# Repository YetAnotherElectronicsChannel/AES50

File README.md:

# AES50 VHDL IP
An implementation of the AES50 protocol in vanilla VHDL.

## About the IP
I started developing this IP around end of 2024 - originally with some other intention.   
However I decided to make this project public with the purpose to be used in the fabulous [OpenX32 project](https://github.com/OpenMixerProject/OpenX32).  
Therefore, this IP was developed fully independent/separated from the OpenX32 project and comes instead with a reference implementation on a custom PCB (also included in this repo) designed around an [Efinix Trion T20 FPGA](https://www.efinixinc.com/shop/t20.php).  
Integration into the OpenX32 project is still a to-do work.. But I'm sure those guys will manage :)

## AES50 Specification
Before asking any detailed questions about functionality or implementation of this IP, please make sure you read and understood the public available AES50 specification which can be downloaded [here](https://aes2.org/publications/standards-store/?id=45).    
Otherwise I might not answer to your request.

## Features of the IP
- Audio-Formats
  - 48kHz / 24-Bit
  - 44.1kHz / 24-Bit
- Audio-Interfaces
  - TDM-8 (6x In + 6x Out) for full 48x48 channel access
  - I2S (1x In + 1x Out) for a reduced 2x2 channel access (the other 46x46 channels are ignored)
- Support for Aux-Data-Tunnel (which is e.g. used for headamp control) over TDM or UART
  - Tunnels the auxiliary data channel through the TDM interface  
  - Send and receive data to/from the auxiliary data tunnel via UART 
- Operation Modes
  - AES50-Master + TDM/I2S Master (Timing Reference: Local Oscillator)
  - AES50-Master + TDM/I2S Slave  (Timing Reference: External I2S/TDM Device)
  - AES50-Slave  + TDM/I2S Master (Timing-Reference: External AES50 Device)
- PLL Support
  - Integrated I2C-controller and driver for Cirrus Logic CS2100CP PLL
- Compatibility / Real-Life Tested
  - Proven to work with X32, Wing, S- and DL- series stageboxes
  - Flawless handling of Cat-Cable Hot-Plugging

### IP Internal Structure    

### Use Case A: 48x48 Channel with Multi-TDM8 Interface and Aux-Data via Uart

### Use Case B: 2x2 Channel with simple I2S Interface and Aux-Data via Uart

### Use Case C: 48x48 Channel with Multi-TDM8 Interface and Aux-Data via TDM8

### Top-Module Ports Description
| Signal                     | Direction | Type                          | Description                             |
| -------------------------- | -------- | ------------------------------ | --------------------------------------- |
| **clk50_i**                | in       | `std_logic`                    | 50 MHz Clock for the Ethernet Logic     |
| **clk100_i**               | in       | `std_logic`                    | 100 MHz Clock for the Core Logic        |
| **rst_i**                  | in       | `std_logic`                    | Synchronous Reset (100 MHz clock-domain)|
| **fs_mode_i**              | in       | `std_logic_vector(1 downto 0)` | Sample-Rate Select<br><ul><li>00 → 44.1 kHz</li><li>01 → 48 kHz</li><li>10 → n.a.</li><li>11 → n.a.</li></ul>|
| **sys_mode_i**             | in       | `std_logic_vector(1 downto 0)` | System-Mode Select<br><ul><li>00 → AES50 Slave & I2S/TDM Master</li><li>01 → AES50 Master & I2S/TDM Master</li><li>10 → AES50 Master & I2S/TDM Slave</li><li>11 → n.a.</li></ul>|               |
| **tdm8_i2s_mode_i**        | in       | `std_logic`                    | Interface Select<br><ul><li>0 → 48x48 TDM8 (Support for Aux-over-TDM)</li><li>1 → 2x2 I2S (only Aux-over-UART)</li></ul>|
| **aux_tx_tdm_uart_select_i**| in       | `std_logic`                   | Aux-Data-Mode <br><ul><li>0 → Aux-over-TDM</li><li>1 → Aux-over-UART</li></ul>|
| **rmii_crs_dv_i**          | in       | `std_logic`                    | RMII Data Valid Receive from PHY        |
| **rmii_rxd_i**             | in       | `std_logic_vector(1 downto 0)` | RMII Data from PHY                      |
| **rmii_tx_en_o**           | out      | `std_logic`                    | RMII Data Valid Transmit to PHY         |
| **rmii_txd_o**             | out      | `std_logic_vector(1 downto 0)` | RMII Data to PHY                        |
| **phy_rst_n_o**            | out      | `std_logic`                    | PHY Reset (active low)                  |
| **aes50_clk_a_rx_i**       | in       | `std_logic`                    | AES50 Clock A Receive                   |
| **aes50_clk_a_tx_o**       | out      | `std_logic`                    | AES50 Clock A Transmit                  |
| **aes50_clk_a_tx_en_o**    | out      | `std_logic`                    | AES50 Clock A Enable LVDS Output Driver      |
| **aes50_clk_b_rx_i**       | in       | `std_logic`                    | AES50 Clock B Receive                   |
| **aes50_clk_b_tx_o**       | out      | `std_logic`                    | AES50 Clock B Transmit                  |
| **aes50_clk_b_tx_en_o**    | out      | `std_logic`                    | AES50 Clock B Enable LVDS Output Driver      |
| **clk_1024xfs_from_pll_i** | in       | `std_logic`                    | Clock from external PLL (1024× fs)      |
| **pll_lock_n_i**           | in       | `std_logic`                    | External PLL Lock Status (active low)   |
| **clk_to_pll_o**           | out      | `std_logic`                    | Clock to external PLL                   |
| **pll_mult_value_o**       | out      | `natural`                      | External PLL multiplication-factor      |
| **pll_init_busy_i**        | in       | `std_logic`                    | PLL init busy status                    |
| **mclk_o**                 | out      | `std_logic`                    | Master Clock (256x fs) - derived (divided by x4) from PLL - independent of System-Mode Select |
| **wclk_o**                 | out      | `std_logic`                    | Word Clock Output (if our IP is I2S/TDM Master)   |
| **bclk_o**                 | out      | `std_logic`                    | Bit Clock Output  (if our IP is I2S/TDM Master)   |
| **wclk_readback_i**        | in       | `std_logic`                    | Word Clock Readback (direct from FPGA-Pin - always needed)    |
| **bclk_readback_i**        | in       | `std_logic`                    | Bit Clock Readback (direct from FPGA-Pin - always needed)     |
| **wclk_out_en_o**          | out      | `std_logic`                    | Word Clock Output Enable (high if IP is I2S/TDM Master)    |
| **bclk_out_en_o**          | out      | `std_logic`                    | Bit Clock Output Enable (high if IP is I2S/TDM Master)     |
| **tdm_i**                  | in       | `std_logic_vector(6 downto 0)` | 6x TDM8 Data Input + 1x TDM8 Aux Data Input   (only needed in 48x48 mode)               |
| **tdm_o**                  | out      | `std_logic_vector(6 downto 0)` | 6x TDM8 Data Output + 1x TDM8 Aux Data Output   (only needed in 48x48 mode)                    |
| **i2s_i**                  | in       | `std_logic`                    | I2S Input  (only needed in 2x2 mode)                            |
| **i2s_o**                  | out      | `std_logic`                    | I2S Output (only needed in 2x2 mode)                             |
| **aes_ok_o**               | out      | `std_logic`                    | AES50 Link Status  (high when connection established)         |
| **dbg_o**                  | out      | `std_logic_vector(7 downto 0)` | Various internal debug signals                          |
| **uart_o**               	 | out      | `std_logic`                    | UART output (received data from the AES50 AUX tunnel)     |
| **uart_i**               	 | in      | `std_logic`                     | UART input (data to send over AES50 AUX-tunnel)     |
### Aux Data Tunnel
AES50 provides (as part of the protocol) an auxiliary data channel with a fixed bandwidth of roughly 5 Mbit/s (the exact rate depends on the selected sample rate, as the auxiliary data stream is synchronous with the audio transmission).  
According to the AES50 specification, there was a proposal (though not mandatory) to use standard Ethernet frames that could be tunneled through this auxiliary data channel - (ever wondered about the mysterious Ethernet port on the DN9630?) -> Therefore I assume that this proposed approach using virtual Ethernet frames is also used in other AES50 devices on the market.  
However, additional mechanisms are required to transmit Ethernet frames through the auxiliary channel - specifically bit-stuffing and data-scrambling. 

#### Aux Data over TDM  
Since the bitstream is synchronous with the audio transmission, this IP enables sending and receiving the aux-bitstream over the TDM8 interface.  
Internally, the IP handles the bitstream as 16-bit words, and the TDM module distributes the auxiliary data evenly across the eight TDM slots as 24-bit “samples.”  
The extra 8 bits act as an overlay protocol to ensure correct interpretation of the auxiliary words when tunneling them over a 3rd party audio-transportation-medium.  
If the TDM-Aux-RX/TX pins of two instances of this IP are cross-connected, it allows transparent tunneling of the auxiliary data channel as long as synchronicity and bit-consistency is ensured.  
A similar concept appears to be implemented in the Appsys Multiverter, which tunnels AES50 auxiliary data as eight audio channels through a Dante network to maintain head-amp remote control.

- See further details in the TDM module implementation

#### Aux Data over UART
It is also possible to send and receive data over the aux-data-tunnel with a UART connection.         
See here an example print-out of a Wing-Rack connected.    

#### Head Amp Remote Control Example
A small [Arduino example](RPI_Pico_2040_HA_Remote_Example/RPI_Pico_2040_HA_Remote_Example.ino) shows how to self-identify and remotely control the head amps (gain & phantom power) of AES50 devices.

This example uses a Raspberry Pi Pico (RP2040), which acts as a command bridge between a computer and the UART terminal connected to the FPGA/AES50 IP core.  
The device identifies itself as an X32 Full-Size and the head amps can be controlled via a serial terminal using the following command examples:

- `gain:ch1@20` → Sets gain on channel 1 to +20 dB  
- `phantom:ch5@1` → Enables +48V on channel 5  
- `phantom:ch5@0` → Disables +48V on channel 5  

The gain-ranges may be interpreted differently with different devices. You will find some info in the comments of the code-example.  
This example is currently configured for controlling a Wing. Make sure that Remote-HA-Control over AES50 is enabled in the console settings.  

See more information here: [Unofficial Protocol Description](Doc/Unofficial_AES50_AUX_Protocol_for_MusicGroup_Devices.pdf)  

Special thanks to Christian Nöding for reverse-engineering the proprietary protocol and Thomas Zint (Behringer R&D) for helping with the checksum calculation.  

Note: The transmission of channel-names does not work yet.

### Audio Interface Timing

Warning: When this IP is in I2S/TDM slave-mode (sys_mode_i = "10"), make ultimately sure, that BCLK/WCLK is stable before releasing the IP's reset.  
AES50 protocol has a pulse-width modulation mechanism in the outgoing (LVDS-)clock signals which needs to be synchronized to the incoming I2S/TDM clock.  
This is only done once after reset. You must ensure externally, if WCLK/BCLK has changed or was unstable, this IP core runs again through a new reset.

#### I2S
In I2S mode, BCLK is 64*fs : 32-Bit per Slot (24-Bit Audio + 8 Bit Padding).  
3.072 MHz for 48k mode and 2.8224 MHz for 44k1. No other I2S configuration is supported besides this.  
This is valid for all system-modes.

#### TDM-8
BCLK is supposed to be 12.288 MHz for 48k or 11.2896 MHz for 44k1 : 32-Bit per Slot (24-Bit Audio + 8 Bit Padding).  
No other TDM configuration is supported besides this.  
This is valid for all system-modes.

#### TDM-8 Master Timing (when BCLK/WCLK is output)
When the IP is TDM master, the WCLK will be high for 8 BCLK cycles. 

#### TDM-8 Slave Timing (when BCLK/WCLK is input)
WCLK must be only high for one BCLK pulse (but can be longer of course)

### Misc
#### Deviations against the specification
- Bit-Error correction is only implemented on the transmitting side (as AES50 devices on market expects this to be implemented properly), however this IP does not correct bit-errors on receiving side. (I personally don't see this as a critical feature. Basically no other network audio protocol has this implemented)
- AES50 specifies a delay of around 3 sample times IP in- to output (in 44k1, 48k). However this IP processes the audio-samples internally in frames of 6 samples at 48k or 11 samples at 44k1. Therefore the latency is slightly higher
- Clock integrity check: AES50 by default runs the LVDS-clock-signals (through the CAT-wire) bidirectional. Even though it would be technically enough to run the clock only unidrectional from the clock-master to the clock-slave, AES50 uses this to check the integrity of the clock-recovery (PLL) on the AES50-slave-device side. As I understood, the slave-device would be supposed to regenerate the pulse-width modulated clock signal based on the recovered clock and send it back to the master. However this IP just loops the clock back to the master in case it is in slave-configuration. Also as per spec, the AES50 should verify the clock speeds for correctness. This IP has implemented only a more simple timeout-watchdog alike clock integrity checking (on both clock-transmitting and clock-receiving side).
- AES50 also supports other audio-formats and sample-rates (e.g. Bitstream-Audio, 88k2, 96k, etc..). This IP is only usable for 24-Bit PCM-Audio for 44k1 and 48k. However the IP is prepared for later integration of 88k2 and 96k sample-rate. I just didn't do this because I was lacking of suitable devices which support AES50 with 88k2/96k.
- The original AES50 implementation found in commercial devices also seem to differ against the specification (or I understood the specification wrong) in two points I found out so far (by actually reverse engineering it):
  -  The figures for aux-data-packet scrambler / descrambler in the specification seem to be exchanged against each other. The actual data-scrambler is the logic-structure shown in the descrambler-figure and vice-versa
  -  In 48k mode, one LC-segment (352 Bits) should consist of in sum 12 LC-sub-segments with two multiplexed channels of 6 samples each having 2-bit padding after each LC-subsegment and 4-bit padding at the end of the LC-frame.  According to my calculations, one LC-subsegment should be 27-bits long (12* (27Bit LC-Subsegment + 2-Bit Padding))+4-Bit Padding = 352 Bit. However the actual protocol behaves like: (6* (26-Bit LC-Subsegment + 2-Bit Padding + 28-Bit LC-Subsegment + 2-Bit Padding)) + 4-Bit Padding = 352 Bit.

#### TODOs / next steps / not done yet
- Verification of internal clock domain crossings
- Constraining and verification of input- & output timings (RMII, TDM, etc..)
- Bit Transparency Testing
- Refactoring of TDM SerDes
- Implement 88k2/96k mode
- Check why the Arduino Code-Example is not transmitting channel-names correctly.
  
#### Random Info
- The core-clock of this IP can also run at a reduced clock-speed of 80 MHz (instead of 100 MHz) if I2S mode only is used. Some internal timing-reference values must be changed for this (see in the top VHDL module in the efinity project)
- In case, the IP will be used in sys_mode_i="01" (AES-master + TDM/I2S master) only, the external PLL is not necessarily needed and the IP can be tricked to run from a static oscilator with 1024xfs speed.   Connect the static 1024xfs clock to "clk_1024xfs_from_pll_i", make "pll_init_busy_i" and "pll_lock_n_i" to static '0' and just leave "clk_to_pll_o" and "pll_mult_value_o" open.
- sys_mode_i, fs_mode_i and tdm8_i2s_mode_i should not be changed on the fly. If this is changed, the IP needs a new reset.
- Spot the easter-egg in this project :-)

## Test Board Setup
### Overview
In I2S mode, only I0/O0 will be used as in+out.  

### Front View

### FPGA Resource Utilization
This is the resource utilization for a full configuration (all sample-rates and operation modes supported, dual TDM/I2S support, PLL-I2C driver etc.).  
Resource utilization depends on actual used configuration.  
Especially if core is configured for e.g. I2S only operation, the utilization is reduced drastically (the TDM-Serdes is still a rather resource-inefficient implementation as of today).

Reference FPGA: Efinix Trion T20Q100F3 (Speedgrade: 4) using Efinity 2025.1.110.5.9 toolchain.  

## Some technical implementation hints

### Ram Reorder processes in AES50-TX/RX Modules

### Startup Sequencing  
The Startup Sequencing must be timed very precisely.  
The Ethernet frame containing the "2048x ASSM-marker" in the header must be tightly aligned with the modulated-clock-pulses on the LVDS signaling.  
This happens in 48k as follows: The IP waits until the clock-pulse-modulation happens. (It is assumed it will happen again after 2048x WCLK). When the clock-pulse-modulation happened, a timer starts with the duration of approx. 2042x (2048-6) WCLK timeframes.  
Then the TDM-serializer starts recording samples into the FIFO to the AES50-TX-module.  
The AES50-TX-Module waits until 6 samples (basically 288 samples as it is 6 samples * 48 channels) are in the FIFO.  
The first ethernet-frame transmitted after this startup-sequence will contain the ASSM-marker in the frame-header and will be aligned with the 2048x modulated clock-pulse.  
This also explains the mysterious "first_transmit_counter" values on the top-level files.   
  
In 44k1 the same mechanism applies, but with a duration of 2048-11 = 2037 WCLK cycles wait time.

### Testbenches
I also attached now the testbenches I used.  
Please see the testbenches as WIP as I modified them as needed and those testbenches might not work out of the box. So this is more of a "playground" rather than a professional verification testbench.

## License

Copyright (c) 2025 Markus Noll (YetAnotherElectronicsChannel)

This IP core is free software: you can redistribute it and/or modify
it under the terms of the GNU General Public License as published by
the Free Software Foundation, either version 3 of the License, or
(at your option) any later version.

This IP core is distributed in the hope that it will be useful,
but WITHOUT ANY WARRANTY; without even the implied warranty of
MERCHANTABILITY or FITNESS FOR A PARTICULAR PURPOSE. See the
GNU General Public License for more details.

You should have received a copy of the GNU General Public License
along with this IP core. If not, see <https://www.gnu.org/licenses/>.

Any other use — including use in other projects or commercial applications —
is not permitted without a separate written license agreement.

Third-party components included in this repository may be licensed under
different terms (for example, GPLv3). These components retain their
original licenses and are clearly marked in the source header.

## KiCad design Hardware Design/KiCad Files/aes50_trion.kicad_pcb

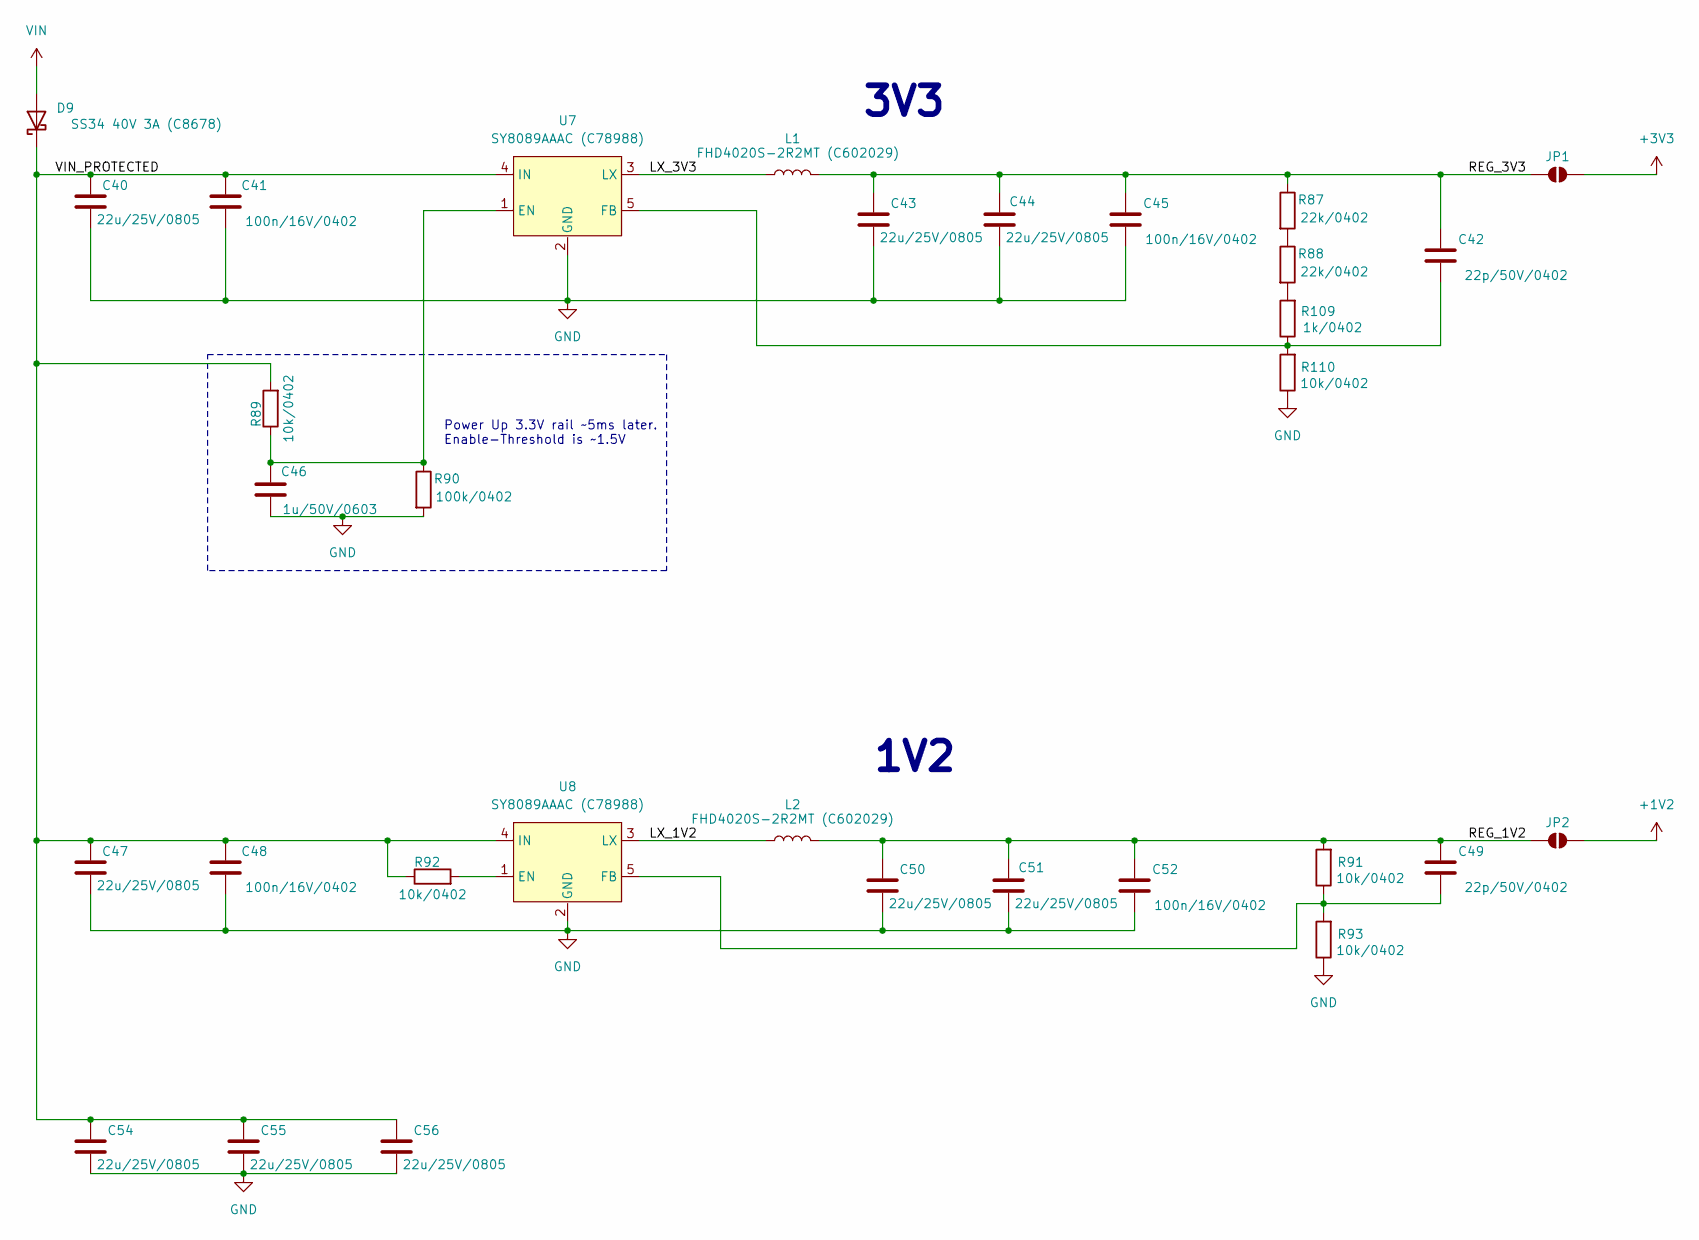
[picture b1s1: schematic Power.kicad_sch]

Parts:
C40, C43, C44, C47, C50, C51, C54, C55, C56: 22u/25V/0805; C_0805_2012Metric
C41, C45, C48, C52: 100n/16V/0402; C_0402_1005Metric
C42, C49: 22p/50V/0402; C_0402_1005Metric
C46: 1u/50V/0603; C_0603_1608Metric
D9: SS34 40V 3A (C8678); D_SMA
JP1, JP2: SolderJumper_2_Open; SolderJumper-2_P1.3mm_Open_RoundedPad1.0x1.5mm
L1, L2: FHD4020S-2R2MT (C602029); L_APV_ANR4020
R87, R88: 22k/0402; R_0402_1005Metric
R89, R91, R92, R93, R110: 10k/0402; R_0402_1005Metric
R90: 100k/0402; R_0402_1005Metric
R109: 1k/0402; R_0402_1005Metric
U7, U8: SY8089AAAC (C78988); SOT-23-5

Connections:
+1V2: JP2.2 (B); also elsewhere on the board
+3V3: JP1.2 (B); also elsewhere on the board
/Power/LX_1V2: L2.1, U8.3 (LX)
/Power/LX_3V3: L1.1, U7.3 (LX)
/Power/REG_1V2: C49.1, C50.1, C51.1, C52.1, JP2.1 (A), L2.2, R91.2
/Power/REG_3V3: C42.1, C43.1, C44.1, C45.1, JP1.1 (A), L1.2, R87.1
/Power/VIN_PROTECTED: C40.1, C41.1, C47.1, C48.1, C54.1, C55.1, C56.1, D9.1 (K), R89.2, R92.1, U7.4 (IN), U8.4 (IN)
GND: C40.2, C41.2, C43.2, C44.2, C45.2, C46.1, C47.2, C48.2, C50.2, C51.2, C52.2, C54.2, C55.2, C56.2, R90.2, R93.1, R110.1, U7.2 (GND), U8.2 (GND); also elsewhere on the board
unnamed: R87.2, R88.1
unnamed: R88.2, R109.2
unnamed: C46.2, R89.1, R90.1, U7.1 (EN)
unnamed: C42.2, R109.1, R110.2, U7.5 (FB)
unnamed: R92.2, U8.1 (EN)
unnamed: C49.2, R91.1, R93.2, U8.5 (FB)
VIN: D9.2 (A); also elsewhere on the board

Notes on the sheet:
3V3
1V2
Power Up 3.3V rail ~5ms later. Enable-Threshold is ~1.5V

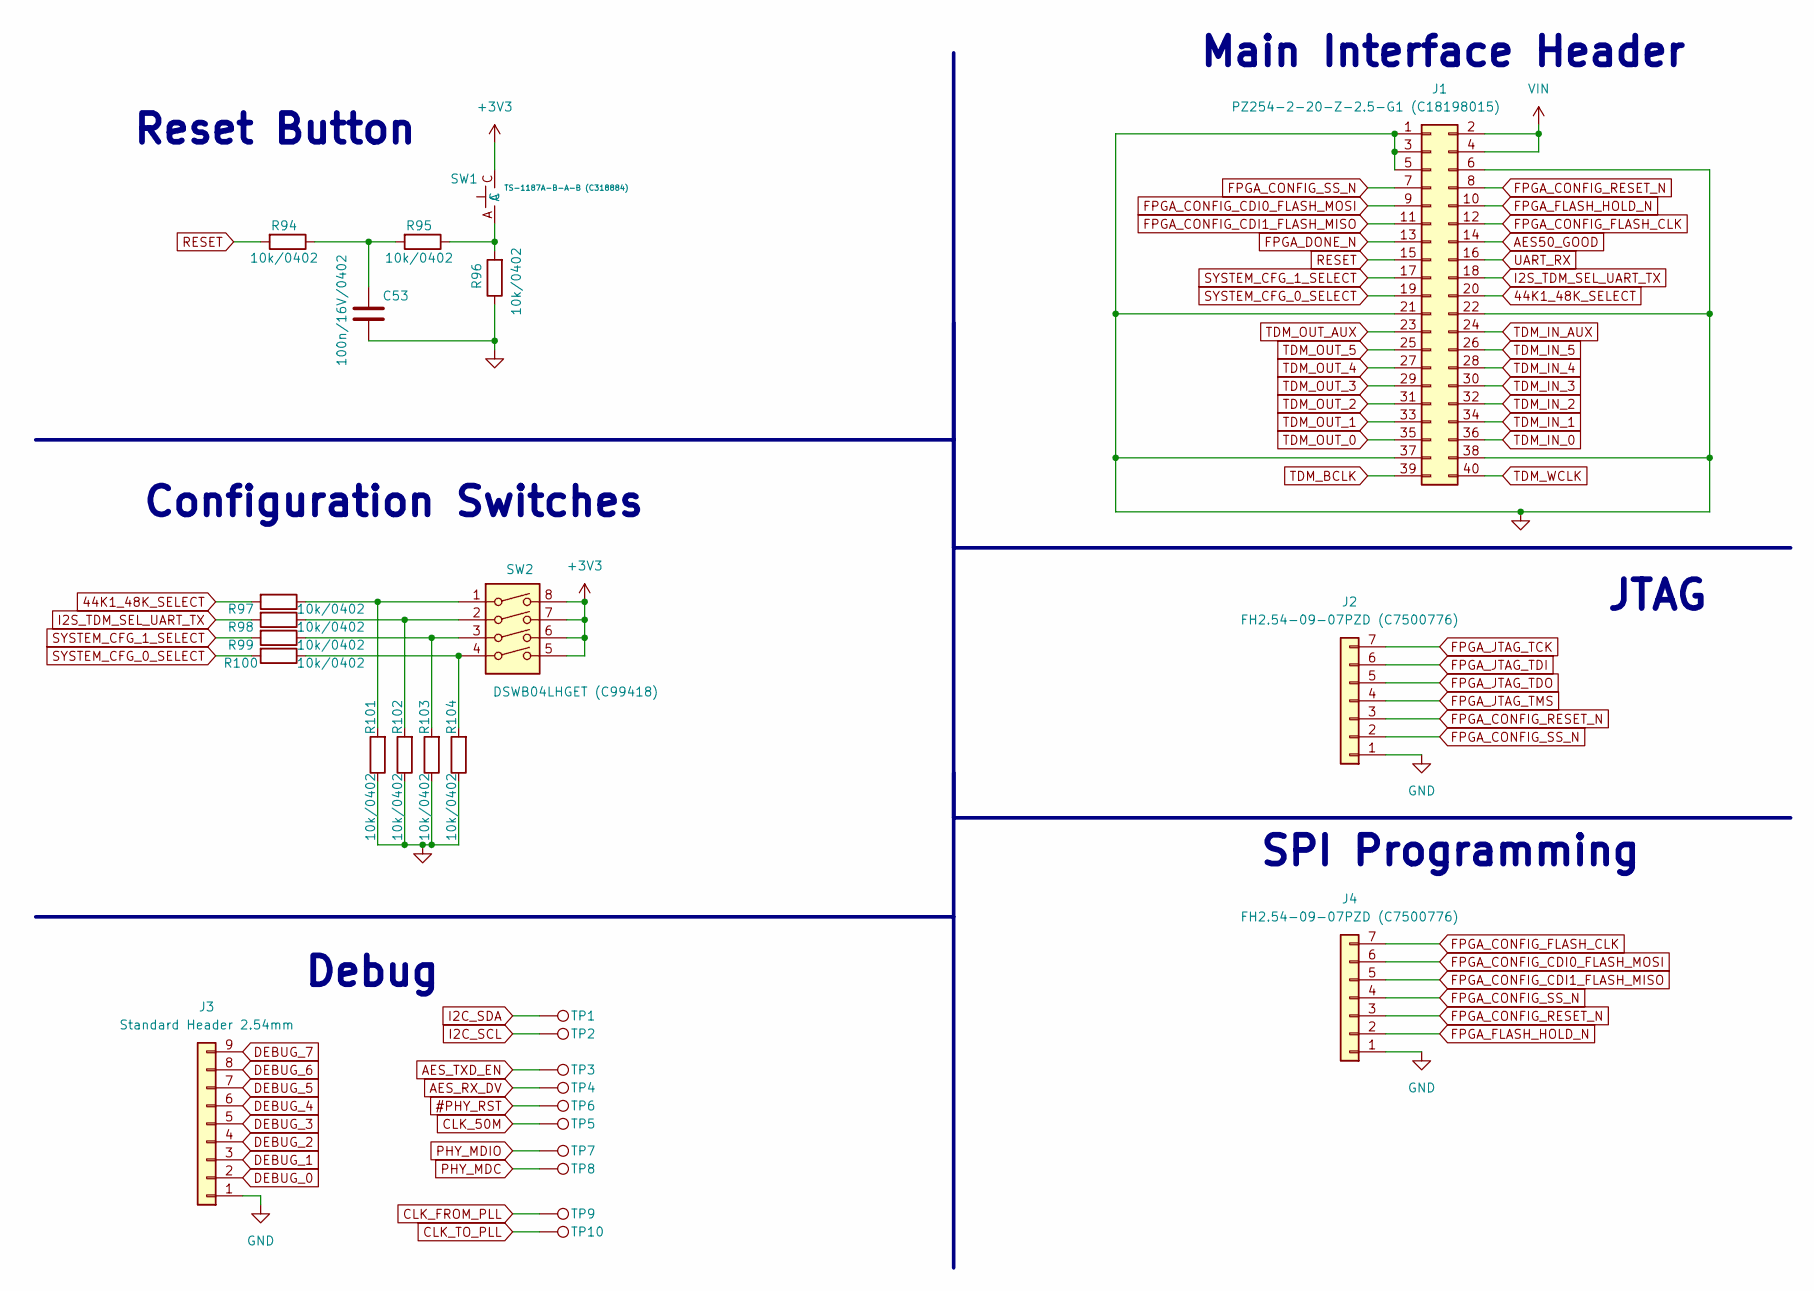
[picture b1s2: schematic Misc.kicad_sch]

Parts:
C53: 100n/16V/0402; C_0402_1005Metric
J1: PZ254-2-20-Z-2.5-G1 (C18198015); PinHeader_2x20_P2.54mm_Vertical
J2, J4: FH2.54-09-07PZD (C7500776); FH2.54-09-07PZD
J3: Standard Header 2.54mm; PinHeader_1x09_P2.54mm_Vertical
R94, R95, R96, R97, R98, R99, R100, R101, R102, R103, R104: 10k/0402; R_0402_1005Metric
SW1: TS-1187A-B-A-B (C318884); TS-1187A-B-A-B
SW2: DSWB04LHGET (C99418); DSWB04LHGET
TP1, TP2, TP3, TP4, TP5, TP6, TP7, TP8, TP9, TP10: TestPoint; TestPoint_Pad_D1.0mm

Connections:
44K1_48K_SELECT: J1.20, R97.2; also elsewhere on the board
#PHY_RST: TP6.1; also elsewhere on the board
+3V3: SW1.C, SW1.D, SW2.5, SW2.6, SW2.7, SW2.8; also elsewhere on the board
AES50_GOOD: J1.14; also elsewhere on the board
AES_RX_DV: TP4.1; also elsewhere on the board
AES_TXD_EN: TP3.1; also elsewhere on the board
CLK_50M: TP5.1; also elsewhere on the board
CLK_FROM_PLL: TP9.1; also elsewhere on the board
CLK_TO_PLL: TP10.1; also elsewhere on the board
DEBUG_0: J3.2; also elsewhere on the board
DEBUG_1: J3.3; also elsewhere on the board
DEBUG_2: J3.4; also elsewhere on the board
DEBUG_3: J3.5; also elsewhere on the board
DEBUG_4: J3.6; also elsewhere on the board
DEBUG_5: J3.7; also elsewhere on the board
DEBUG_6: J3.8; also elsewhere on the board
DEBUG_7: J3.9; also elsewhere on the board
FPGA_CONFIG_CDI0_FLASH_MOSI: J1.9, J4.6; also elsewhere on the board
FPGA_CONFIG_CDI1_FLASH_MISO: J1.11, J4.5; also elsewhere on the board
FPGA_CONFIG_FLASH_CLK: J1.12, J4.7; also elsewhere on the board
FPGA_CONFIG_RESET_N: J1.8, J2.3, J4.3; also elsewhere on the board
FPGA_CONFIG_SS_N: J1.7, J2.2, J4.4; also elsewhere on the board
FPGA_DONE_N: J1.13; also elsewhere on the board
FPGA_FLASH_HOLD_N: J1.10, J4.2; also elsewhere on the board
FPGA_JTAG_TCK: J2.7; also elsewhere on the board
FPGA_JTAG_TDI: J2.6; also elsewhere on the board
FPGA_JTAG_TDO: J2.5; also elsewhere on the board
FPGA_JTAG_TMS: J2.4; also elsewhere on the board
GND: C53.2, J1.1, J1.3, J1.5, J1.6, J1.21, J1.22, J1.37, J1.38, J2.1, J3.1, J4.1, R96.1, R101.1, R102.1, R103.1, R104.1; also elsewhere on the board
I2C_SCL: TP2.1; also elsewhere on the board
I2C_SDA: TP1.1; also elsewhere on the board
unnamed: C53.1, R94.1, R95.2
unnamed: R95.1, R96.2, SW1.A, SW1.B
unnamed: R100.1, R104.2, SW2.4
unnamed: R97.1, R101.2, SW2.1
unnamed: R98.1, R102.2, SW2.2
unnamed: R99.1, R103.2, SW2.3
PHY_MDC: TP8.1; also elsewhere on the board
PHY_MDIO: TP7.1; also elsewhere on the board
RESET: J1.15, R94.2; also elsewhere on the board
SPARE_SELECT_GPIO: J1.18, R98.2; also elsewhere on the board
SYSTEM_CFG_0_SELECT: J1.19, R100.2; also elsewhere on the board
SYSTEM_CFG_1_SELECT: J1.17, R99.2; also elsewhere on the board
TDM_BCLK: J1.39; also elsewhere on the board
TDM_IN_0: J1.36; also elsewhere on the board
TDM_IN_1: J1.34; also elsewhere on the board
TDM_IN_2: J1.32; also elsewhere on the board
TDM_IN_3: J1.30; also elsewhere on the board
TDM_IN_4: J1.28; also elsewhere on the board
TDM_IN_5: J1.26; also elsewhere on the board
TDM_IN_AUX: J1.24; also elsewhere on the board
TDM_OUT_0: J1.35; also elsewhere on the board
TDM_OUT_1: J1.33; also elsewhere on the board
TDM_OUT_2: J1.31; also elsewhere on the board
TDM_OUT_3: J1.29; also elsewhere on the board
TDM_OUT_4: J1.27; also elsewhere on the board
TDM_OUT_5: J1.25; also elsewhere on the board
TDM_OUT_AUX: J1.23; also elsewhere on the board
TDM_WCLK: J1.40; also elsewhere on the board
UART_TX: J1.16; also elsewhere on the board
VIN: J1.2, J1.4; also elsewhere on the board

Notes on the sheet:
Reset Button
Main Interface Header
Configuration Switches
JTAG
SPI Programming
Debug

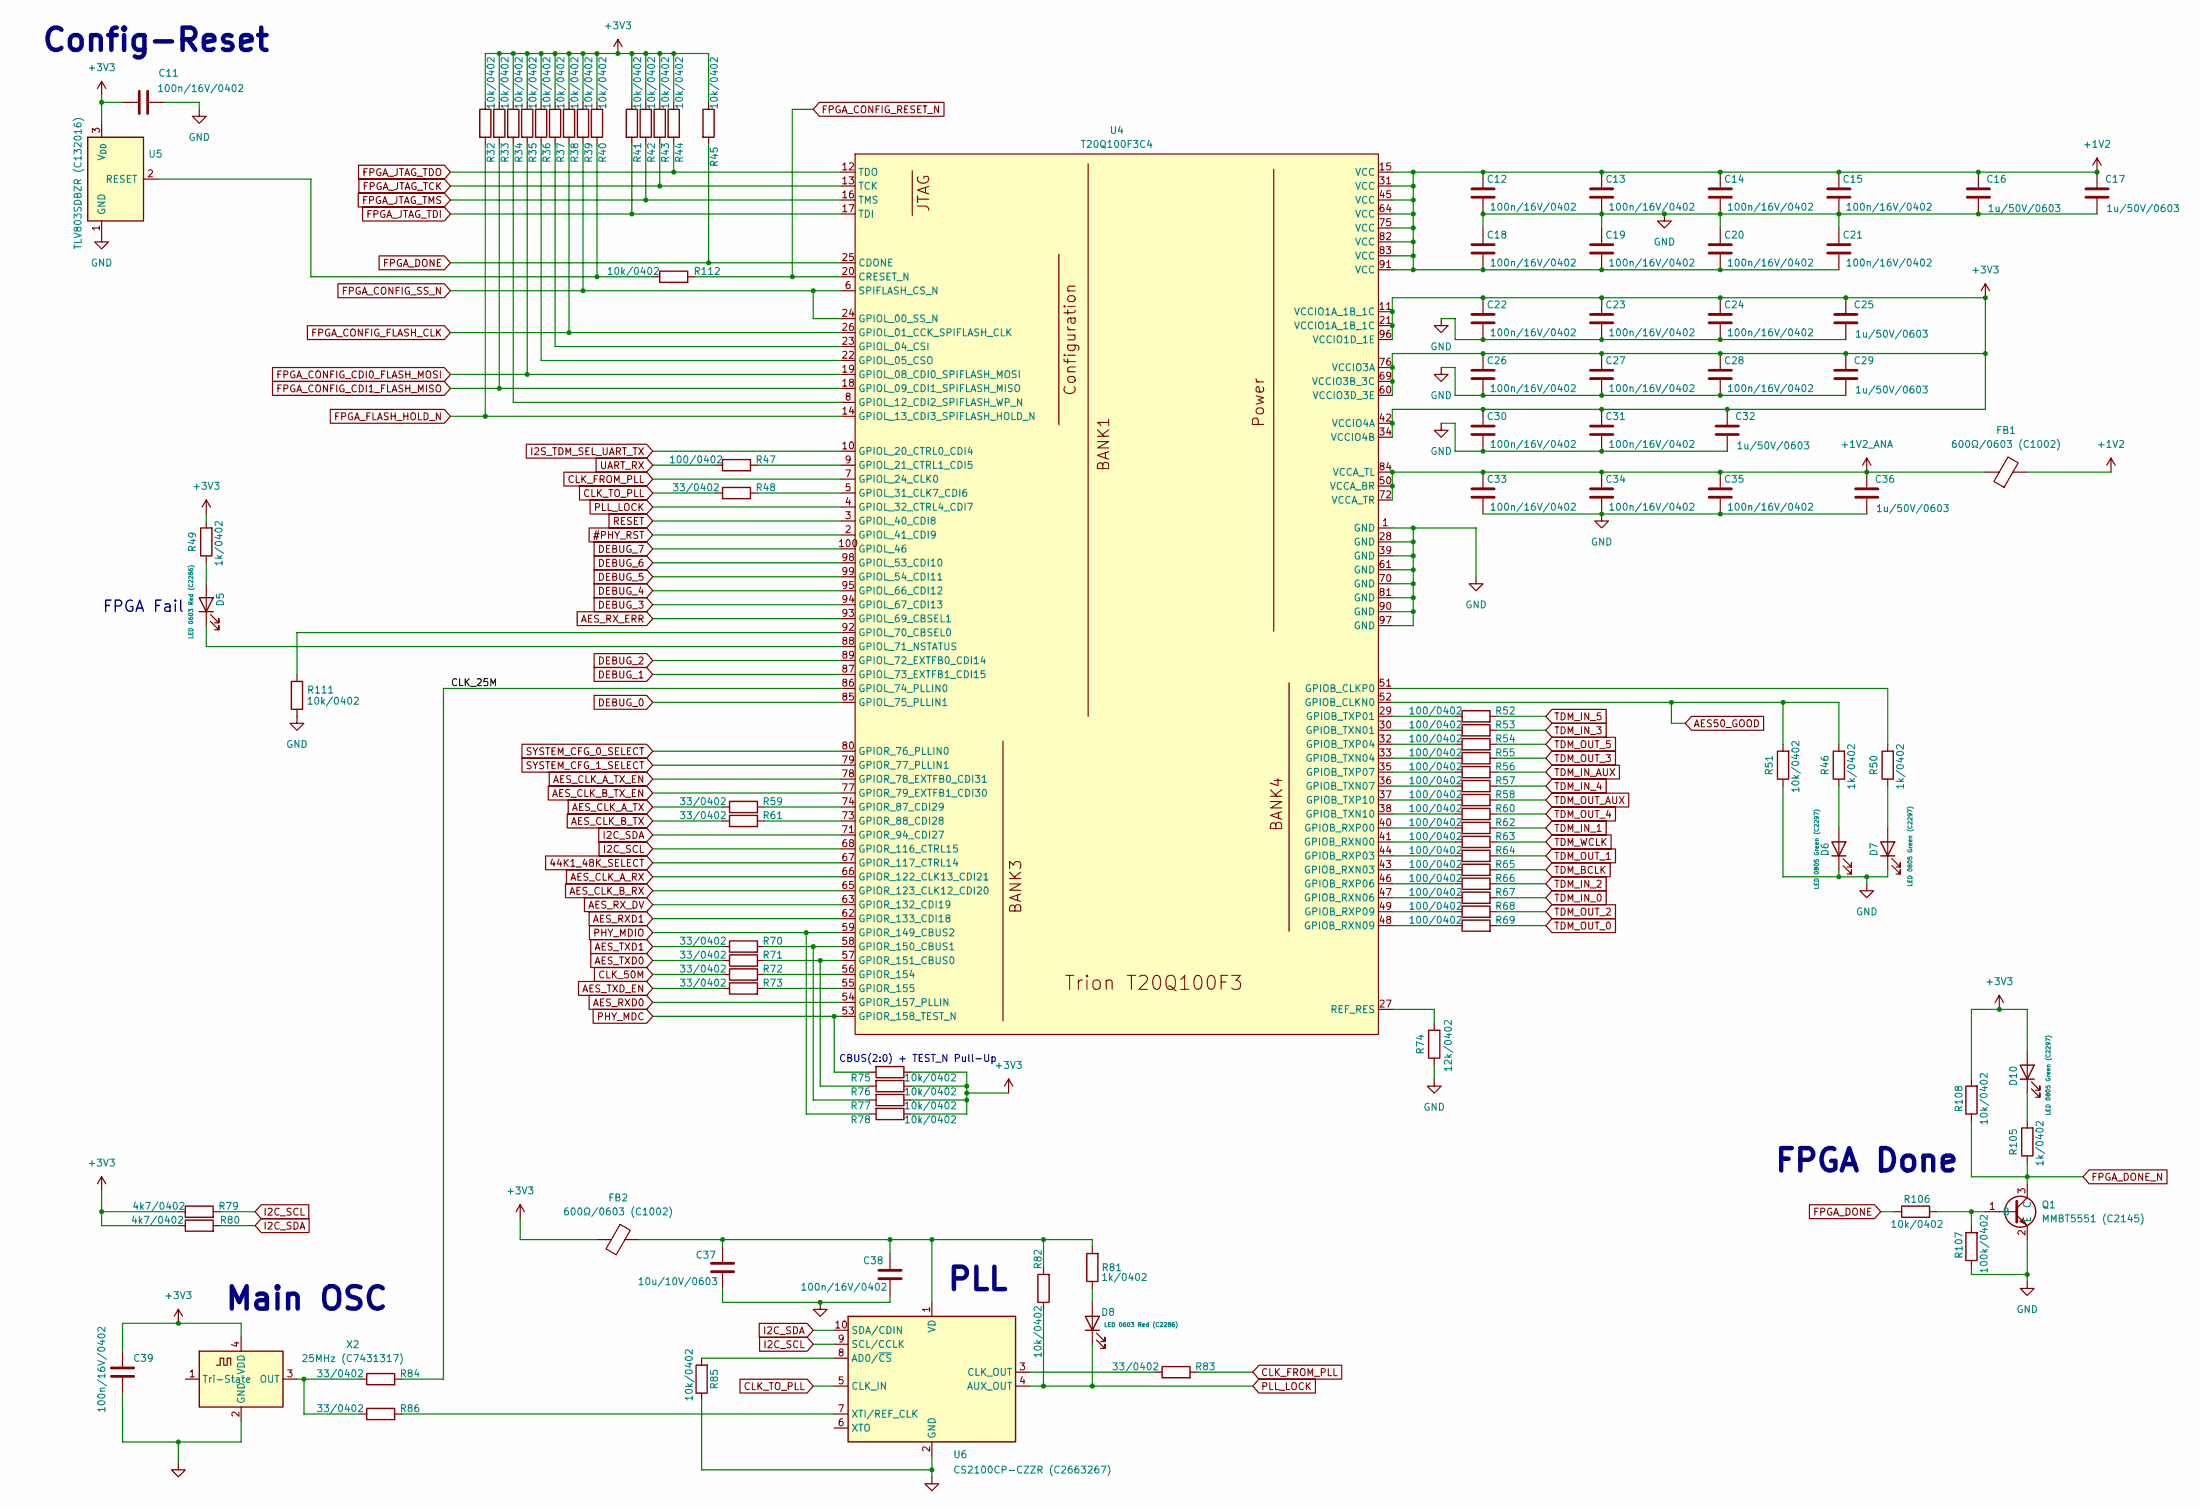
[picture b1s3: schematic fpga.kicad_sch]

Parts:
C11, C12, C13, C14, C15, C18, C19, C20, C21, C22, C23, C24, C26, C27, C28, C30, C31, C33, C34, C35, C38, C39: 100n/16V/0402; C_0402_1005Metric
C16, C17, C25, C29, C32, C36: 1u/50V/0603; C_0603_1608Metric
C37: 10u/10V/0603; C_0603_1608Metric
D5, D8: LED 0603 Red (C2286); LED_0603_1608Metric
D6, D7, D10: LED 0805 Green (C2297); LED_0805_2012Metric
FB1, FB2: 600Ω/0603 (C1002); L_0603_1608Metric
Q1: MMBT5551 (C2145); SOT-23
R32, R33, R34, R35, R36, R37, R38, R39, R40, R41, R42, R43, R44, R45, R51, R75, R76, R77, R78, R82, R85, R106, R108, R111, R112: 10k/0402; R_0402_1005Metric
R46, R49, R50, R81, R105: 1k/0402; R_0402_1005Metric
R47, R52, R53, R54, R55, R56, R57, R58, R60, R62, R63, R64, R65, R66, R67, R68, R69: 100/0402; R_0402_1005Metric
R48, R59, R61, R70, R71, R72, R73, R83, R84, R86: 33/0402; R_0402_1005Metric
R74: 12k/0402; R_0402_1005Metric
R79, R80: 4k7/0402; R_0402_1005Metric
R107: 100k/0402; R_0402_1005Metric
U4: T20Q100F3C4; LQFP-100_14x14mm_P0.5mm
U5: TLV803SDBZR (C132016); SOT-23
U6: CS2100CP-CZZR (C2663267); MSOP-10_3x3mm_P0.5mm
X2: 25MHz (C7431317); Oscillator_SMD_ECS_2520MV-xxx-xx-4Pin_2.5x2.0mm

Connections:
44K1_48K_SELECT: U4.67 (GPIOR_117_CTRL14); also elsewhere on the board
#PHY_RST: U4.2 (GPIOL_41_CDI9); also elsewhere on the board
+1V2: C12.2, C13.2, C14.2, C15.2, C16.2, C17.2, C18.1, C19.1, C20.1, C21.1, FB1.2, U4.15 (VCC), U4.31 (VCC), U4.45 (VCC), U4.64 (VCC), U4.75 (VCC), U4.82 (VCC), U4.83 (VCC), U4.91 (VCC); also elsewhere on the board
+1V2_ANA: C33.2, C34.2, C35.2, C36.2, FB1.1, U4.50 (VCCA_BR), U4.72 (VCCA_TR), U4.84 (VCCA_TL)
+3V3: C11.2, C22.2, C23.2, C24.2, C25.2, C26.2, C27.2, C28.2, C29.2, C30.2, C31.2, C32.2, C39.1, D10.2 (A), FB2.2, R32.1, R33.1, R34.1, R35.1, R36.1, R37.1, R38.1, R39.1, R40.1, R41.1, R42.1, R43.1, R44.1, R45.1, R49.2, R75.1, R76.1, R77.1, R78.1, R79.1, R80.1, R108.2, U4.11 (VCCIO1A_1B_1C), U4.21 (VCCIO1A_1B_1C), U4.34 (VCCIO4B), U4.42 (VCCIO4A), U4.60 (VCCIO3D_3E), U4.69 (VCCIO3B_3C), U4.76 (VCCIO3A), U4.96 (VCCIO1D_1E), U5.3 (V_{DD}), X2.4 (VDD); also elsewhere on the board
/FPGA/CLK_25M: R84.2, U4.86 (GPIOL_74_PLLIN0)
AES50_GOOD: R46.2, R51.2, U4.52 (GPIOB_CLKN0); also elsewhere on the board
AES_CLK_A_RX: U4.66 (GPIOR_122_CLK13_CDI21); also elsewhere on the board
AES_CLK_A_TX: R59.1; also elsewhere on the board
AES_CLK_A_TX_EN: U4.78 (GPIOR_78_EXTFB0_CDI31); also elsewhere on the board
AES_CLK_B_RX: U4.65 (GPIOR_123_CLK12_CDI20); also elsewhere on the board
AES_CLK_B_TX: R61.1; also elsewhere on the board
AES_CLK_B_TX_EN: U4.77 (GPIOR_79_EXTFB1_CDI30); also elsewhere on the board
AES_RXD0: U4.54 (GPIOR_157_PLLIN); also elsewhere on the board
AES_RXD1: U4.62 (GPIOR_133_CDI18); also elsewhere on the board
AES_RX_DV: U4.63 (GPIOR_132_CDI19); also elsewhere on the board
AES_RX_ERR: U4.93 (GPIOL_69_CBSEL1); also elsewhere on the board
AES_TXD0: R71.1; also elsewhere on the board
AES_TXD1: R70.1; also elsewhere on the board
AES_TXD_EN: R73.1; also elsewhere on the board
CLK_50M: R72.1; also elsewhere on the board
CLK_FROM_PLL: R83.2, U4.7 (GPIOL_24_CLK0); also elsewhere on the board
CLK_TO_PLL: R48.1, U6.5 (CLK_IN); also elsewhere on the board
DEBUG_0: U4.85 (GPIOL_75_PLLIN1); also elsewhere on the board
DEBUG_1: U4.87 (GPIOL_73_EXTFB1_CDI15); also elsewhere on the board
DEBUG_2: U4.89 (GPIOL_72_EXTFB0_CDI14); also elsewhere on the board
DEBUG_3: U4.94 (GPIOL_67_CDI13); also elsewhere on the board
DEBUG_4: U4.95 (GPIOL_66_CDI12); also elsewhere on the board
DEBUG_5: U4.99 (GPIOL_54_CDI11); also elsewhere on the board
DEBUG_6: U4.98 (GPIOL_53_CDI10); also elsewhere on the board
DEBUG_7: U4.100 (GPIOL_46); also elsewhere on the board
FPGA_CONFIG_CDI0_FLASH_MOSI: R35.2, U4.19 (GPIOL_08_CDI0_SPIFLASH_MOSI); also elsewhere on the board
FPGA_CONFIG_CDI1_FLASH_MISO: R33.2, U4.18 (GPIOL_09_CDI1_SPIFLASH_MISO); also elsewhere on the board
FPGA_CONFIG_FLASH_CLK: R38.2, U4.26 (GPIOL_01_CCK_SPIFLASH_CLK); also elsewhere on the board
FPGA_CONFIG_RESET_N: R112.2, U4.20 (CRESET_N); also elsewhere on the board
FPGA_CONFIG_SS_N: R39.2, U4.6 (SPIFLASH_CS_N), U4.24 (GPIOL_00_SS_N); also elsewhere on the board
FPGA_DONE: R45.2, R106.1, U4.25 (CDONE)
FPGA_DONE_N: Q1.3 (C), R105.1, R108.1; also elsewhere on the board
FPGA_FLASH_HOLD_N: R32.2, U4.14 (GPIOL_13_CDI3_SPIFLASH_HOLD_N); also elsewhere on the board
FPGA_JTAG_TCK: R43.2, U4.13 (TCK); also elsewhere on the board
FPGA_JTAG_TDI: R41.2, U4.17 (TDI); also elsewhere on the board
FPGA_JTAG_TDO: R44.2, U4.12 (TDO); also elsewhere on the board
FPGA_JTAG_TMS: R42.2, U4.16 (TMS); also elsewhere on the board
GND: C11.1, C12.1, C13.1, C14.1, C15.1, C16.1, C17.1, C18.2, C19.2, C20.2, C21.2, C22.1, C23.1, C24.1, C25.1, C26.1, C27.1, C28.1, C29.1, C30.1, C31.1, C32.1, C33.1, C34.1, C35.1, C36.1, C37.1, C38.2, C39.2, D6.1 (K), D7.1 (K), Q1.2 (E), R51.1, R74.1, R85.1, R107.1, R111.1, U4.1 (GND), U4.28 (GND), U4.39 (GND), U4.61 (GND), U4.70 (GND), U4.81 (GND), U4.90 (GND), U4.97 (GND), U5.1 (GND), U6.2 (GND), X2.2 (GND); also elsewhere on the board
I2C_SCL: R79.2, U4.68 (GPIOR_116_CTRL15), U6.9 (SCL/CCLK); also elsewhere on the board
I2C_SDA: R80.2, U4.71 (GPIOR_94_CDI27), U6.10 (SDA/CDIN); also elsewhere on the board
unnamed: D5.2 (A), R49.1
unnamed: D5.1 (K), U4.88 (GPIOL_71_NSTATUS)
unnamed: D6.2 (A), R46.1
unnamed: D7.2 (A), R50.1
unnamed: D8.2 (A), R81.1
unnamed: D10.1 (K), R105.2
unnamed: Q1.1 (B), R106.2, R107.2
unnamed: R50.2, U4.51 (GPIOB_CLKP0)
unnamed: R63.1, U4.41 (GPIOB_RXN00)
unnamed: R65.1, U4.43 (GPIOB_RXN03)
unnamed: R67.1, U4.47 (GPIOB_RXN06)
unnamed: R69.1, U4.48 (GPIOB_RXN09)
unnamed: R62.1, U4.40 (GPIOB_RXP00)
unnamed: R64.1, U4.44 (GPIOB_RXP03)
unnamed: R66.1, U4.46 (GPIOB_RXP06)
unnamed: R68.1, U4.49 (GPIOB_RXP09)
unnamed: R53.1, U4.30 (GPIOB_TXN01)
unnamed: R55.1, U4.33 (GPIOB_TXN04)
unnamed: R57.1, U4.36 (GPIOB_TXN07)
unnamed: R60.1, U4.38 (GPIOB_TXN10)
unnamed: R52.1, U4.29 (GPIOB_TXP01)
unnamed: R54.1, U4.32 (GPIOB_TXP04)
unnamed: R56.1, U4.35 (GPIOB_TXP07)
unnamed: R58.1, U4.37 (GPIOB_TXP10)
unnamed: R37.2, U4.23 (GPIOL_04_CSI)
unnamed: R36.2, U4.22 (GPIOL_05_CSO)
unnamed: R34.2, U4.8 (GPIOL_12_CDI2_SPIFLASH_WP_N)
unnamed: R47.2, U4.9 (GPIOL_21_CTRL1_CDI5)
unnamed: R48.2, U4.5 (GPIOL_31_CLK7_CDI6)
unnamed: R111.2, U4.92 (GPIOL_70_CBSEL0)
unnamed: R59.2, U4.74 (GPIOR_87_CDI29)
unnamed: R61.2, U4.73 (GPIOR_88_CDI28)
unnamed: R70.2, R77.2, U4.58 (GPIOR_150_CBUS1)
unnamed: R71.2, R76.2, U4.57 (GPIOR_151_CBUS0)
unnamed: R72.2, U4.56 (GPIOR_154)
unnamed: R73.2, U4.55 (GPIOR_155)
unnamed: R74.2, U4.27 (REF_RES)
unnamed: R40.2, R112.1, U5.2 (RESET)
unnamed: R85.2, U6.8 (AD0/~CS)
unnamed: R83.1, U6.3 (CLK_OUT)
unnamed: C37.2, C38.1, FB2.1, R81.2, R82.2, U6.1 (VD)
unnamed: R86.2, U6.7 (XTI/REF_CLK)
unnamed: R84.1, R86.1, X2.3 (OUT)
PHY_MDC: R75.2, U4.53 (GPIOR_158_TEST_N); also elsewhere on the board
PHY_MDIO: R78.2, U4.59 (GPIOR_149_CBUS2); also elsewhere on the board
PLL_LOCK: D8.1 (K), R82.1, U4.4 (GPIOL_32_CTRL4_CDI7), U6.4 (AUX_OUT)
RESET: U4.3 (GPIOL_40_CDI8); also elsewhere on the board
SPARE_SELECT_GPIO: U4.10 (GPIOL_20_CTRL0_CDI4); also elsewhere on the board
SYSTEM_CFG_0_SELECT: U4.80 (GPIOR_76_PLLIN0); also elsewhere on the board
SYSTEM_CFG_1_SELECT: U4.79 (GPIOR_77_PLLIN1); also elsewhere on the board
TDM_BCLK: R65.2; also elsewhere on the board
TDM_IN_0: R67.2; also elsewhere on the board
TDM_IN_1: R62.2; also elsewhere on the board
TDM_IN_2: R66.2; also elsewhere on the board
TDM_IN_3: R53.2; also elsewhere on the board
TDM_IN_4: R57.2; also elsewhere on the board
TDM_IN_5: R52.2; also elsewhere on the board
TDM_IN_AUX: R56.2; also elsewhere on the board
TDM_OUT_0: R69.2; also elsewhere on the board
TDM_OUT_1: R64.2; also elsewhere on the board
TDM_OUT_2: R68.2; also elsewhere on the board
TDM_OUT_3: R55.2; also elsewhere on the board
TDM_OUT_4: R60.2; also elsewhere on the board
TDM_OUT_5: R54.2; also elsewhere on the board
TDM_OUT_AUX: R58.2; also elsewhere on the board
TDM_WCLK: R63.2; also elsewhere on the board
UART_TX: R47.1; also elsewhere on the board

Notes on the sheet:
PLL
FPGA Fail
Main OSC
Config-Reset
FPGA Done
CBUS(2:0) + TEST_N Pull-Up
